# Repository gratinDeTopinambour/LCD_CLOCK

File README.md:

# ⏱️ LCD_CLOCK

A complete **open-source low-power LCD clock project** based on the **STM32U083RCT6** microcontroller.

This repository contains all the resources required to build the project:

- 📐 **3D Design**: Enclosure and mechanical parts for 3D printing.
- 🔌 **Electronics**: Schematics, PCB layout, BOM, Gerbers, and PDF documentation.
- 💻 **Firmware**: Embedded C software developed using STM32CubeIDE / STM32CubeMX.
- 🖥️ **LCD Display**: Direct driving of a 4-digit LCD display by the STM32.
- ⏰ **Timekeeping**: Utilizes the internal RTC and low-frequency LSE oscillator.
- 🔋 **Power Management**: Leverages low-power peripherals and STOP2 sleep mode.
- 🌡️ **Analog Measurements**: Temperature and battery voltage monitoring via ADC.
- 📖 **Documentation**: Technical files and documents needed for manufacturing and development.

---

## 🖼️ Project Overview

| LCD Clock |
| :---: |
|  |
|  |

---

## 📂 Project Structure

```text
LCD_CLOCK/
│
├── 3D_design/                             # Mechanical design
│   ├── LCD_Clock_back.stl                 # Back part of the enclosure
│   ├── LCD_Clock_button_lumiere.stl       # Light control button
│   ├── LCD_Clock_button.stl               # Control button
│   ├── LCD_Clock_capot.stl                # Enclosure top cover
│   ├── LCD_Clock_dessous.stl              # Bottom part of the enclosure
│   ├── LCD_Clock_face_avant.stl           # Front panel
│   ├── LCD_Clock.3mf                      # Complete 3D project / model
│   └── LCD_Clock.step                     # STEP CAD model
│
├── Electronics/                           # Electronics design
│   ├── BOM/                               # Bill of Materials
│   ├── GERBER/                            # PCB manufacturing files
│   ├── KICAD/                             # KiCad project
│   └── PDF_version/                       # PDF electronics documentation
│
├── pictures/                              # Project photos
│   ├── 20260919_160751.jpg
│   └── 20260919_161016.jpg
│
├── Program/                               # STM32 firmware
│   ├── .settings/                         # STM32CubeIDE settings
│   ├── Core/                              # Application code and configuration
│   ├── Drivers/                           # Drivers and libraries
│   ├── .cproject                          # Eclipse project configuration
│   ├── .mxproject                         # STM32CubeMX configuration
│   ├── .project                           # STM32CubeIDE project file
│   ├── LCD_CLOCK Debug.launch             # Debug launch configuration
│   ├── LCD_CLOCK.ioc                      # STM32CubeMX configuration file
│   └── STM32U083RCTX_FLASH.ld             # Linker script
│
├── README.md                              # Main documentation
└── LICENSE                                # Project license

---

## ⚡ Technical Specifications

* **Microcontroller**: STM32U083RCT6 (Ultra-low-power ARM Cortex-M0+).
* **Display**: 4-digit LCD directly driven by the microcontroller.
* **Timekeeping**: RTC with LSE low-frequency oscillator.
* **Low Power**: Leverages RTC/LPTIM peripherals and STOP2 mode.
* **Measurements**: Temperature and battery voltage measured via ADC.
* **PCB Design**: Designed with **KiCad**, Gerber files and BOM included.
* **Power Supply**: Designed for battery operation.

---

## 🖨️ 3D Printed Enclosure

Parts are located in the `3D_design/` directory.

| Part | Format | Description |
| :--- | :--- | :--- |
| `LCD_Clock.3mf` | `.3mf` | 3D enclosure model |
| `LCD_Clock.step` | `.step` | CAD enclosure model |
| `LCD_Clock_capot.stl` | `.stl` | Top cover |
| `LCD_Clock_face_avant.stl` | `.stl` | Front panel |
| `LCD_Clock_back.stl` | `.stl` | Back part |
| `LCD_Clock_dessous.stl` | `.stl` | Bottom part |
| `LCD_Clock_button.stl` | `.stl` | Control button |
| `LCD_Clock_button_lumiere.stl` | `.stl` | Light control button |

---

## 💻 Firmware & Development

Source code is located in `Program/`.

### Prerequisites

* [STM32CubeIDE](https://www.st.com/en/development-tools/stm32cubeide.html) (recent version)
* Debugger / Programmer (ST-Link V2 / V3)

### Building and Flashing

1. Open **STM32CubeIDE**.
2. Import the project from `Program/`.
3. If you wish to modify peripheral configurations, open the `LCD_CLOCK.ioc` file.
4. Build (`Build Project`) then flash the microcontroller using the included debug configuration (`LCD_CLOCK Debug.launch`).

---

## 🏭 PCB Manufacturing

To manufacture the PCB:

1. Production-ready manufacturing files are located in `Electronics/GERBER/`.
2. The Bill of Materials (BOM) is available in `Electronics/BOM/`.
3. Original design files are available in `Electronics/KICAD/`.
4. Schematics and documentation are available in `Electronics/PDF_version/`.

---

## 📖 Documentation

Technical documentation for this project can be found in the `Electronics/PDF_version/` and `Program/` directories.

---

## 📜 License

This project is released under an open-source license. You are free to use, modify, and distribute it.

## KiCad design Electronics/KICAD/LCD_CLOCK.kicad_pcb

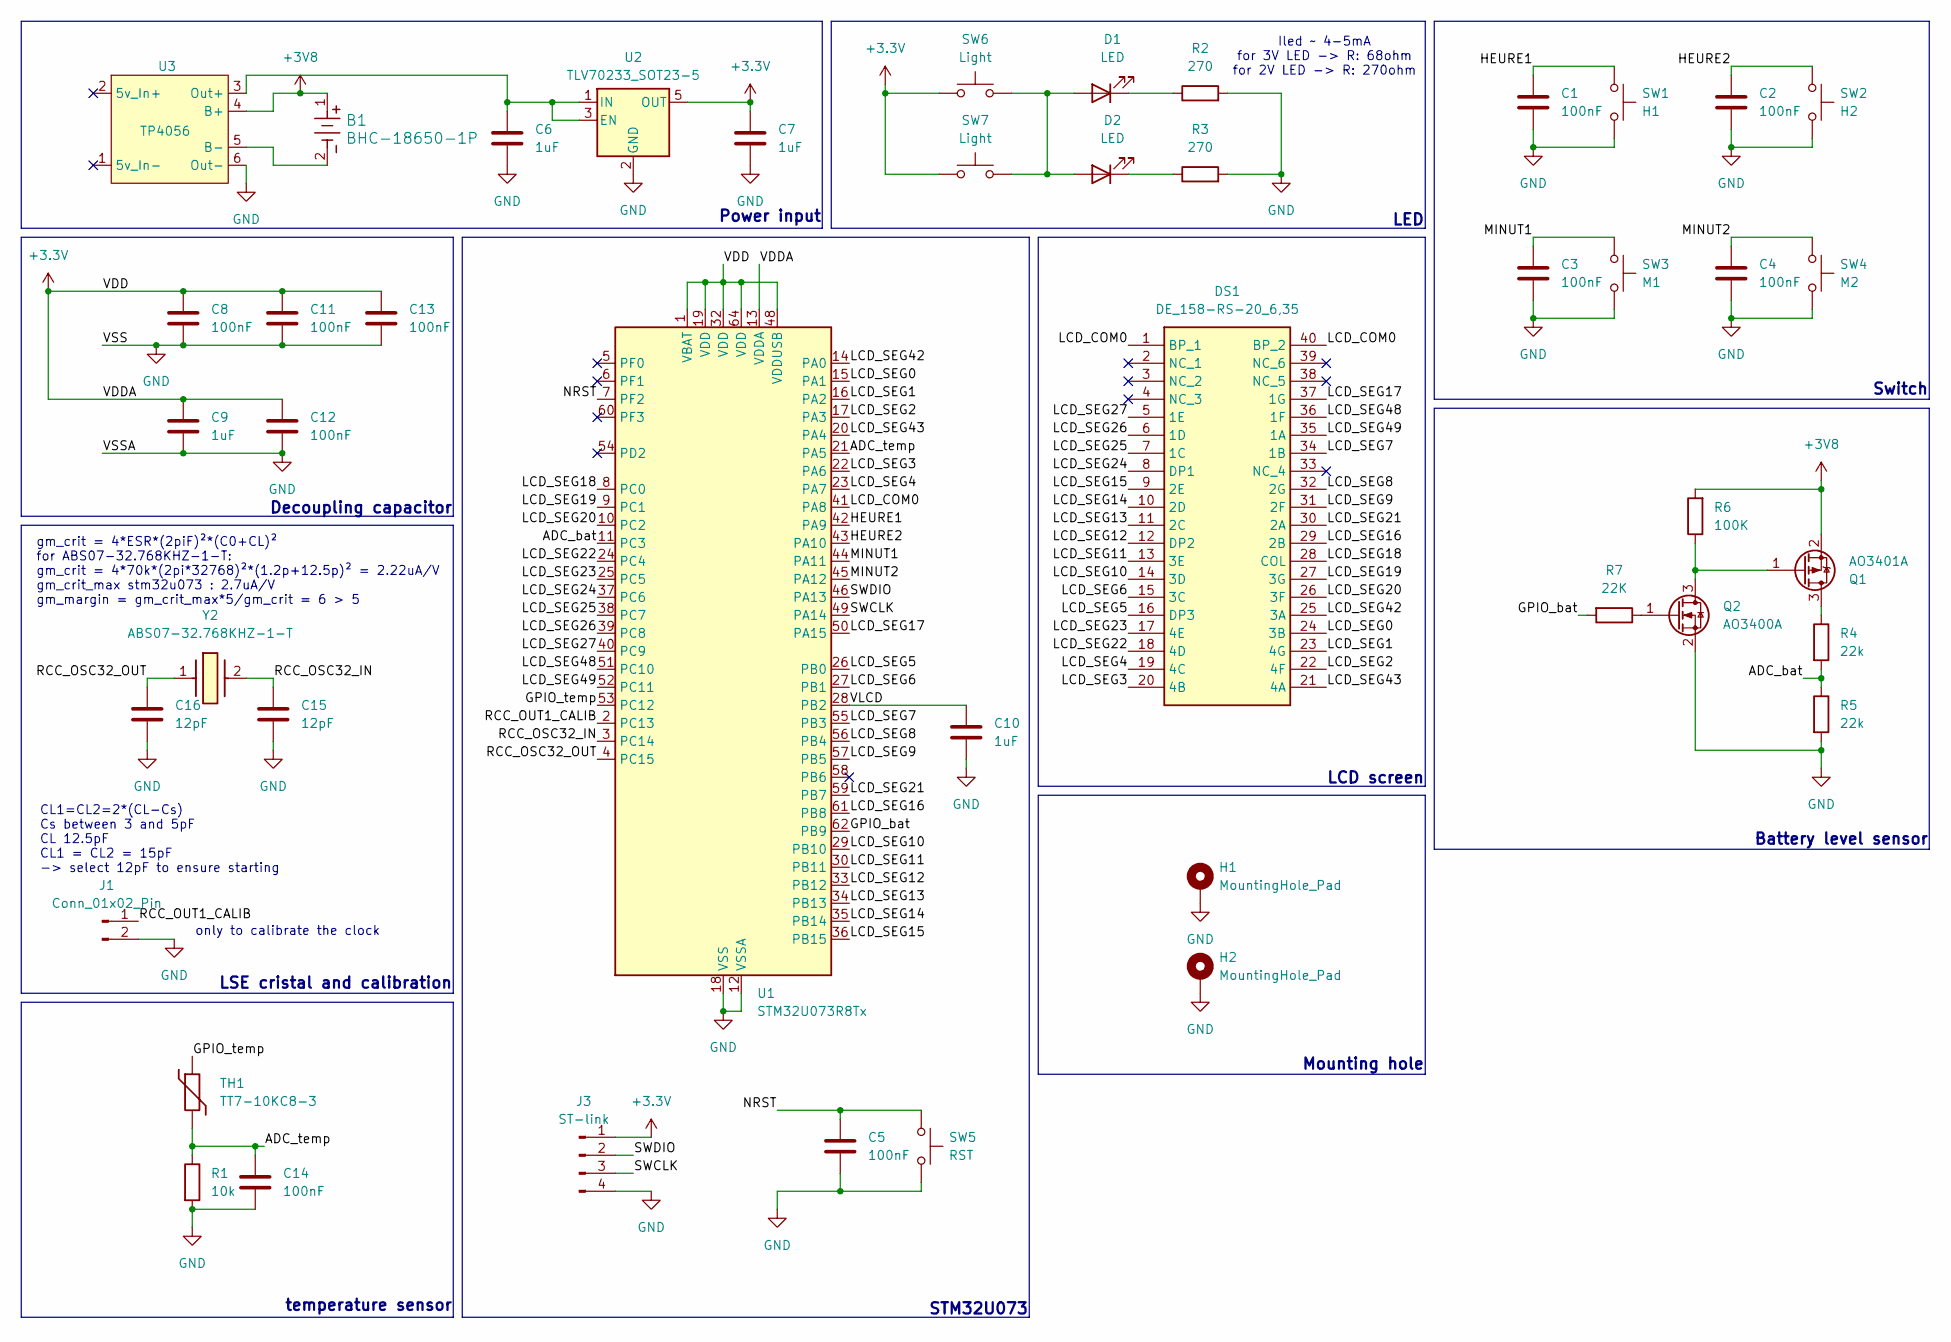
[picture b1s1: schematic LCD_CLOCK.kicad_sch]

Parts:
B1: BHC-18650-1P; BHC-18650-1P_COM
C1, C2, C3, C4, C5: 100nF; C_Disc_D5.0mm_W2.5mm_P5.00mm
C6, C7, C9, C10: 1uF; C_0603_1608Metric
C8, C11, C12: 100nF; C_0603_1608Metric
C13, C14: 100nF; C_0805_2012Metric
C15, C16: 12pF; C_0402_1005Metric
D1, D2: LED; LED_D5.0mm
DS1: DE_158-RS-20_6,35; DE158RS20635; Manufacturer_Part_Number DE 158-RS-20/6,35
H1, H2: MountingHole_Pad; MountingHole_3.2mm_M3_Pad_Via
J1: Conn_01x02_Pin; PinHeader_1x02_P2.54mm_Vertical
J3: ST-link; PinHeader_1x04_P2.54mm_Vertical
Q1: AO3401A; SOT-23
Q2: AO3400A; SOT-23
R1: 10k; R_0805_2012Metric
R2, R3: 270; R_Axial_DIN0207_L6.3mm_D2.5mm_P7.62mm_Horizontal
R4, R5: 22k; R_0603_1608Metric
R6: 100K; R_Axial_DIN0207_L6.3mm_D2.5mm_P7.62mm_Horizontal
R7: 22K; R_Axial_DIN0207_L6.3mm_D2.5mm_P7.62mm_Horizontal
SW1: H1; SW_PUSH_6mm_H5mm
SW2: H2; SW_PUSH_6mm_H5mm
SW3: M1; SW_PUSH_6mm_H5mm
SW4: M2; SW_PUSH_6mm_H5mm
SW5: RST; SW_PUSH_6mm_H5mm
SW6, SW7: Light; SW_PUSH_6mm_H5mm
TH1: TT7-10KC8-3; R_Axial_DIN0204_L3.6mm_D1.6mm_P2.54mm_Vertical
U1: STM32U073R8Tx; LQFP-64_10x10mm_P0.5mm
U2: TLV70233_SOT23-5; SOT-23-5
U3: TP4056; Module_TP4056
Y2: ABS07-32.768KHZ-1-T; ABS07; Manufacturer_Part_Number ABS07-32.768KHZ-1-T

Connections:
+3.3V: C7.1, C8.1, C9.1, C11.1, C12.1, C13.1, J3.1, SW6.1, SW7.1, U1.1 (VBAT), U1.13 (VDDA), U1.19 (VDD), U1.32 (VDD), U1.48 (VDDUSB), U1.64 (VDD), U2.5 (OUT)
+3V8: B1.1, Q1.2 (S), R6.2, U3.4 (B+)
/ADC_bat: R4.2, R5.1, U1.11 (PC3)
/ADC_temp: C14.1, R1.1, TH1.2, U1.21 (PA5)
/GPIO_bat: R7.2, U1.62 (PB9)
/GPIO_temp: TH1.1, U1.53 (PC12)
/HEURE1: C1.2, SW1.1, U1.42 (PA9)
/HEURE2: C2.2, SW2.1, U1.43 (PA10)
/LCD_COM0: DS1.1 (BP_1), DS1.40 (BP_2), U1.41 (PA8)
/LCD_SEG0: DS1.24 (3B), U1.15 (PA1)
/LCD_SEG1: DS1.23 (4G), U1.16 (PA2)
/LCD_SEG2: DS1.22 (4F), U1.17 (PA3)
/LCD_SEG3: DS1.20 (4B), U1.22 (PA6)
/LCD_SEG4: DS1.19 (4C), U1.23 (PA7)
/LCD_SEG5: DS1.16 (DP3), U1.26 (PB0)
/LCD_SEG6: DS1.15 (3C), U1.27 (PB1)
/LCD_SEG7: DS1.34 (1B), U1.55 (PB3)
/LCD_SEG8: DS1.32 (2G), U1.56 (PB4)
/LCD_SEG9: DS1.31 (2F), U1.57 (PB5)
/LCD_SEG10: DS1.14 (3D), U1.29 (PB10)
/LCD_SEG11: DS1.13 (3E), U1.30 (PB11)
/LCD_SEG12: DS1.12 (DP2), U1.33 (PB12)
/LCD_SEG13: DS1.11 (2C), U1.34 (PB13)
/LCD_SEG14: DS1.10 (2D), U1.35 (PB14)
/LCD_SEG15: DS1.9 (2E), U1.36 (PB15)
/LCD_SEG16: DS1.29 (2B), U1.61 (PB8)
/LCD_SEG17: DS1.37 (1G), U1.50 (PA15)
/LCD_SEG18: DS1.28 (COL), U1.8 (PC0)
/LCD_SEG19: DS1.27 (3G), U1.9 (PC1)
/LCD_SEG20: DS1.26 (3F), U1.10 (PC2)
/LCD_SEG21: DS1.30 (2A), U1.59 (PB7)
/LCD_SEG22: DS1.18 (4D), U1.24 (PC4)
/LCD_SEG23: DS1.17 (4E), U1.25 (PC5)
/LCD_SEG24: DS1.8 (DP1), U1.37 (PC6)
/LCD_SEG25: DS1.7 (1C), U1.38 (PC7)
/LCD_SEG26: DS1.6 (1D), U1.39 (PC8)
/LCD_SEG27: DS1.5 (1E), U1.40 (PC9)
/LCD_SEG42: DS1.25 (3A), U1.14 (PA0)
/LCD_SEG43: DS1.21 (4A), U1.20 (PA4)
/LCD_SEG48: DS1.36 (1F), U1.51 (PC10)
/LCD_SEG49: DS1.35 (1A), U1.52 (PC11)
/MINUT1: C3.2, SW3.1, U1.44 (PA11)
/MINUT2: C4.2, SW4.1, U1.45 (PA12)
/NRST: C5.2, SW5.1, U1.7 (PF2)
/RCC_OSC32_IN: C15.1, U1.3 (PC14), Y2.2
/RCC_OSC32_OUT: C16.1, U1.4 (PC15), Y2.1
/RCC_OUT1_CALIB: J1.1, U1.2 (PC13)
/SWCLK: J3.3, U1.49 (PA14)
/SWDIO: J3.2, U1.46 (PA13)
/VLCD: C10.1, U1.28 (PB2)
GND: C1.1, C2.1, C3.1, C4.1, C5.1, C6.2, C7.2, C8.2, C9.2, C10.2, C11.2, C12.2, C13.2, C14.2, C15.2, C16.2, H1.1 (1_1), H2.1 (1_1), J1.2, J3.4, Q2.2 (S), R1.2, R2.2, R3.2, R5.2, SW1.2, SW2.2, SW3.2, SW4.2, SW5.2, U1.12 (VSSA), U1.18 (VSS), U1.31 (VSS), U1.47 (VSS), U1.63 (VSS), U2.2 (GND), U3.6 (Out-)
unnamed: D1.2 (A), D2.2 (A), SW6.2, SW7.2
unnamed: D1.1 (K), R2.1
unnamed: D2.1 (K), R3.1
unnamed: Q1.3 (D), R4.1
unnamed: Q1.1 (G), Q2.3 (D), R6.1
unnamed: Q2.1 (G), R7.1
unnamed: C6.1, U2.1 (IN), U2.3 (EN), U3.3 (Out+)
unnamed: B1.2, U3.5 (B-)

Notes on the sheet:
LCD screen
Power input
Battery level sensor
LED
Switch
Iled ~ 4-5mA for 3V LED -> R: 68ohm for 2V LED -> R: 270ohm
CL1=CL2=2*(CL-Cs) Cs between 3 and 5pF CL 12.5pF CL1 = CL2 = 15pF -> select 12pF to ensure starting
STM32U073
Decoupling capacitor
LSE cristal and calibration
Mounting hole
temperature sensor
gm_crit = 4*ESR*(2piF)²*(C0+CL)² for ABS07-32.768KHZ-1-T: gm_crit = 4*70k*(2pi*32768)²*(1.2p+12.5p)² = 2.22uA/V gm_crit_max stm32u073 : 2.7uA/V gm_margin = gm_crit_max*5/gm_crit = 6 > 5
only to calibrate the clock

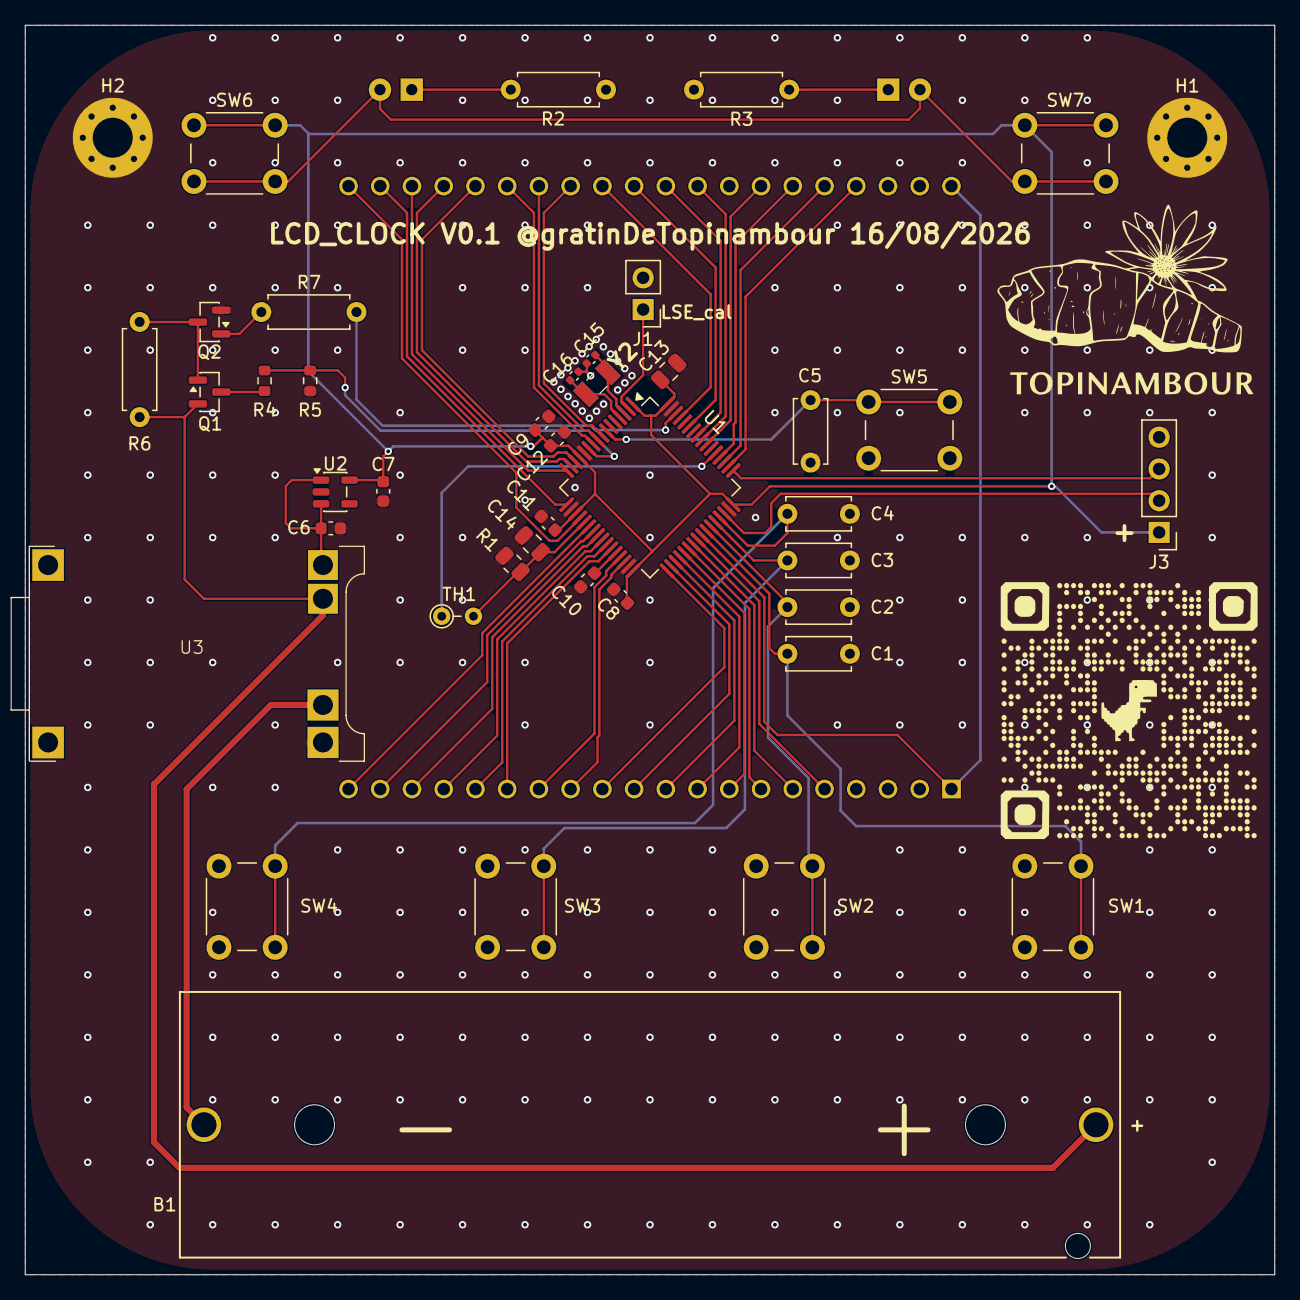
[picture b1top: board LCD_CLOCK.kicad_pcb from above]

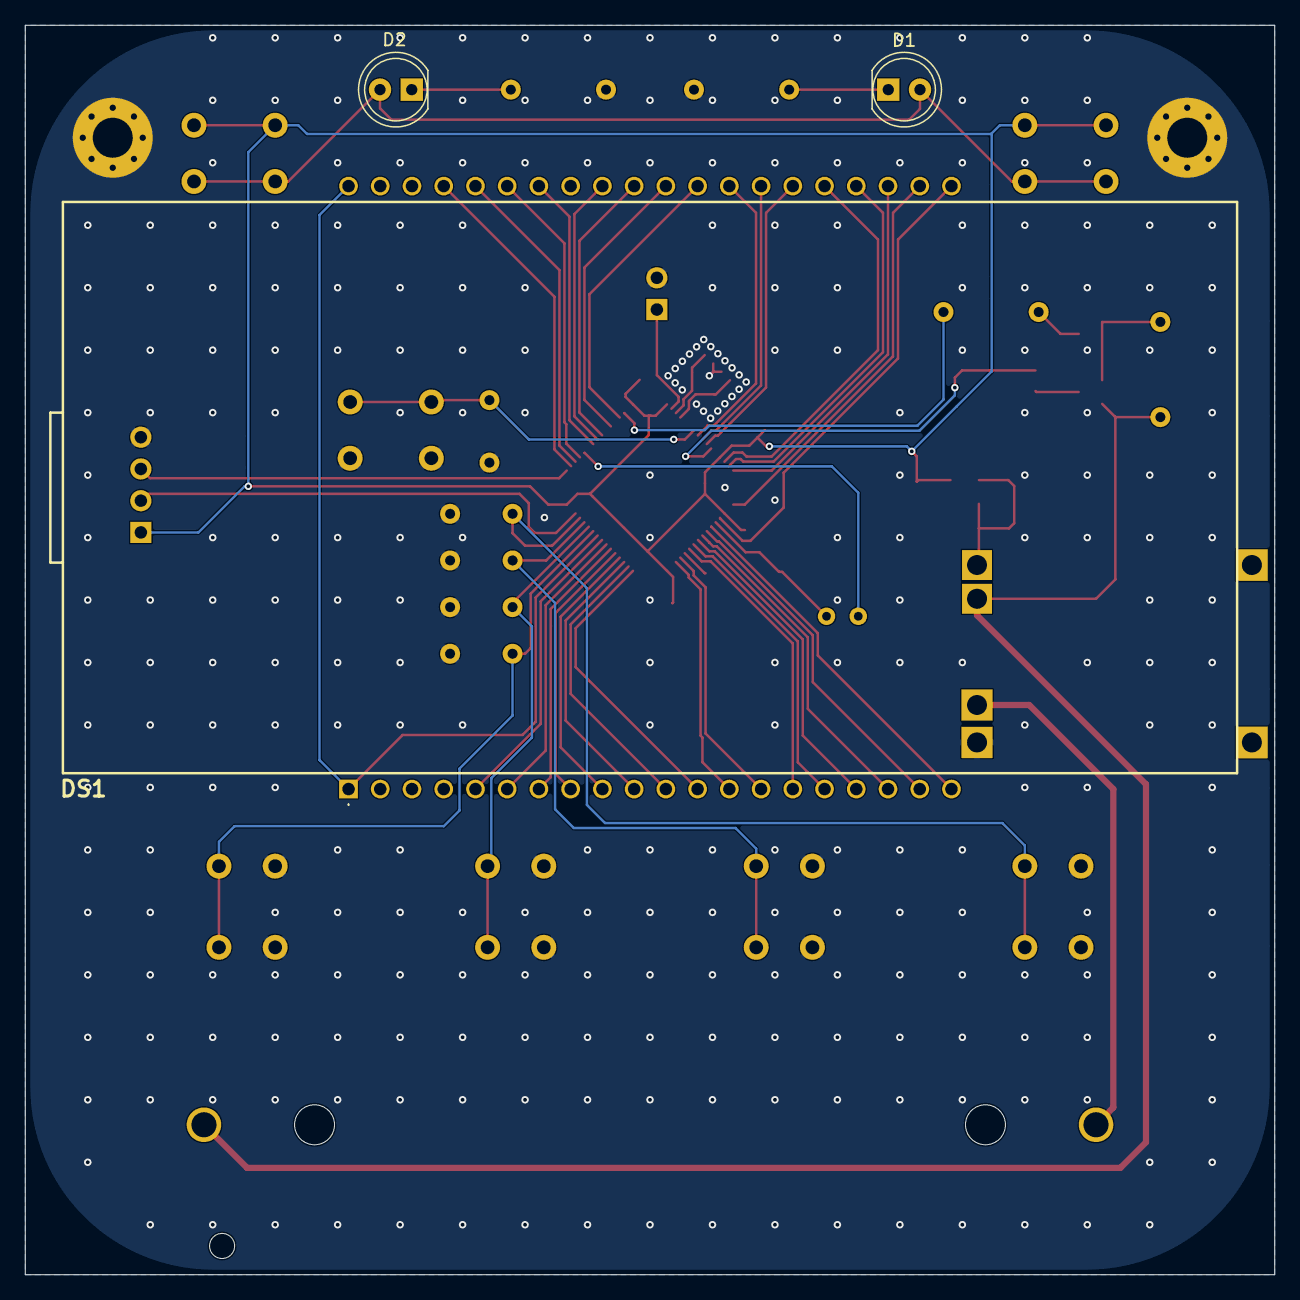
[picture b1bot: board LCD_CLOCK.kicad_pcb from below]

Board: 2 copper layers, 100.0 x 100.0 mm, 45 parts (3 on the bottom side), 59 nets.

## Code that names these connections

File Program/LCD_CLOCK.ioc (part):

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Mcu.Name=STM32U083RCTx
Mcu.Package=LQFP64
Mcu.UserName=STM32U083RCTx
PA0.Mode=SEG42
PA0.Signal=LCD_SEG42
PA1.Mode=SEG0
PA1.Signal=LCD_SEG0
PA10.GPIOParameters=GPIO_PuPd,GPIO_Label,GPIO_ModeDefaultEXTI
PA10.GPIO_Label=HEURE2
PA10.GPIO_ModeDefaultEXTI=GPIO_MODE_IT_FALLING
PA10.GPIO_PuPd=GPIO_PULLUP
PA10.Signal=GPXTI10
PA11\ [PA9].GPIOParameters=GPIO_PuPd,GPIO_Label,GPIO_ModeDefaultEXTI
PA11\ [PA9].GPIO_Label=MINUT1
PA11\ [PA9].GPIO_ModeDefaultEXTI=GPIO_MODE_IT_FALLING
PA11\ [PA9].GPIO_PuPd=GPIO_PULLUP
PA11\ [PA9].Signal=GPXTI11
PA12\ [PA10].GPIOParameters=GPIO_PuPd,GPIO_Label,GPIO_ModeDefaultEXTI
PA12\ [PA10].GPIO_Label=MINUT2
PA12\ [PA10].GPIO_ModeDefaultEXTI=GPIO_MODE_IT_FALLING
PA12\ [PA10].GPIO_PuPd=GPIO_PULLUP
PA12\ [PA10].Signal=GPXTI12
PA15.Mode=SEG17
PA15.Signal=LCD_SEG17
PA2.Mode=SEG1
PA2.Signal=LCD_SEG1
PA3.Mode=SEG2
PA3.Signal=LCD_SEG2
PA4.Mode=SEG43
PA4.Signal=LCD_SEG43
PA5.GPIOParameters=GPIO_Label
PA5.GPIO_Label=TEMP_ADC
PA5.Mode=IN9
PA5.Signal=ADC1_IN9
PA6.Mode=SEG3
PA6.Signal=LCD_SEG3
PA7.Mode=SEG4
PA7.Signal=LCD_SEG4
PA8.Mode=Static
PA8.Signal=LCD_COM0
PA9.GPIOParameters=GPIO_PuPd,GPIO_Label,GPIO_ModeDefaultEXTI
PA9.GPIO_Label=HEURE1
PA9.GPIO_ModeDefaultEXTI=GPIO_MODE_IT_FALLING
PA9.GPIO_PuPd=GPIO_PULLUP
PA9.Signal=GPXTI9
PB0.Mode=SEG5
PB0.Signal=LCD_SEG5
PB1.Mode=SEG6
PB1.Signal=LCD_SEG6
PB10.Mode=SEG10
PB10.Signal=LCD_SEG10
PB11.Mode=SEG11
PB11.Signal=LCD_SEG11
PB12.Mode=SEG12
PB12.Signal=LCD_SEG12
PB13.Mode=SEG13
PB13.Signal=LCD_SEG13
PB14.Mode=SEG14
PB14.Signal=LCD_SEG14
PB15.Mode=SEG15
PB15.Signal=LCD_SEG15
PB2.Mode=Static
PB2.Signal=LCD_VLCD
PB3.Mode=SEG7
PB3.Signal=LCD_SEG7
PB4.Mode=SEG8
PB4.Signal=LCD_SEG8
PB5.Mode=SEG9
PB5.Signal=LCD_SEG9
PB7.Mode=SEG21
PB7.Signal=LCD_SEG21
PB8.Mode=SEG16
PB8.Signal=LCD_SEG16
PB9.GPIOParameters=GPIO_Label
PB9.GPIO_Label=BAT_ADC_ENABLE
PB9.Signal=GPIO_Output
PC0.Mode=SEG18
PC0.Signal=LCD_SEG18
PC1.Mode=SEG19
PC1.Signal=LCD_SEG19
PC10.Mode=SEG48
PC10.Signal=LCD_SEG48
PC11.Mode=SEG49
PC11.Signal=LCD_SEG49
PC12.GPIOParameters=GPIO_Label
PC12.GPIO_Label=TEMP_ADC_ENABLE
PC12.Signal=GPIO_Output
PC13.Mode=Calibration_1Hz
PC13.Signal=RTC_OUT1
PC14-OSC32_IN.Mode=LSE-External-Oscillator
PC14-OSC32_IN.Signal=RCC_OSC32_IN
PC15-OSC32_OUT.Mode=LSE-External-Oscillator
PC15-OSC32_OUT.Signal=RCC_OSC32_OUT
PC2.Mode=SEG20
PC2.Signal=LCD_SEG20
PC3.GPIOParameters=GPIO_Label
PC3.GPIO_Label=BAT_ADC
PC3.Mode=IN3
PC3.Signal=ADC1_IN3
PC4.Mode=SEG22
PC4.Signal=LCD_SEG22
PC5.Mode=SEG23
PC5.Signal=LCD_SEG23
PC6.Mode=SEG24
PC6.Signal=LCD_SEG24
PC7.Mode=SEG25
PC7.Signal=LCD_SEG25
PC8.Mode=SEG26
PC8.Signal=LCD_SEG26
PC9.Mode=SEG27
PC9.Signal=LCD_SEG27
RCC.HSE_VALUE=4000000
RCC.SYSCLKFreq_VALUE=16000000
board=custom
